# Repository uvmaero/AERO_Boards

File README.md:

# AERO_Boards
All the Boards We Make

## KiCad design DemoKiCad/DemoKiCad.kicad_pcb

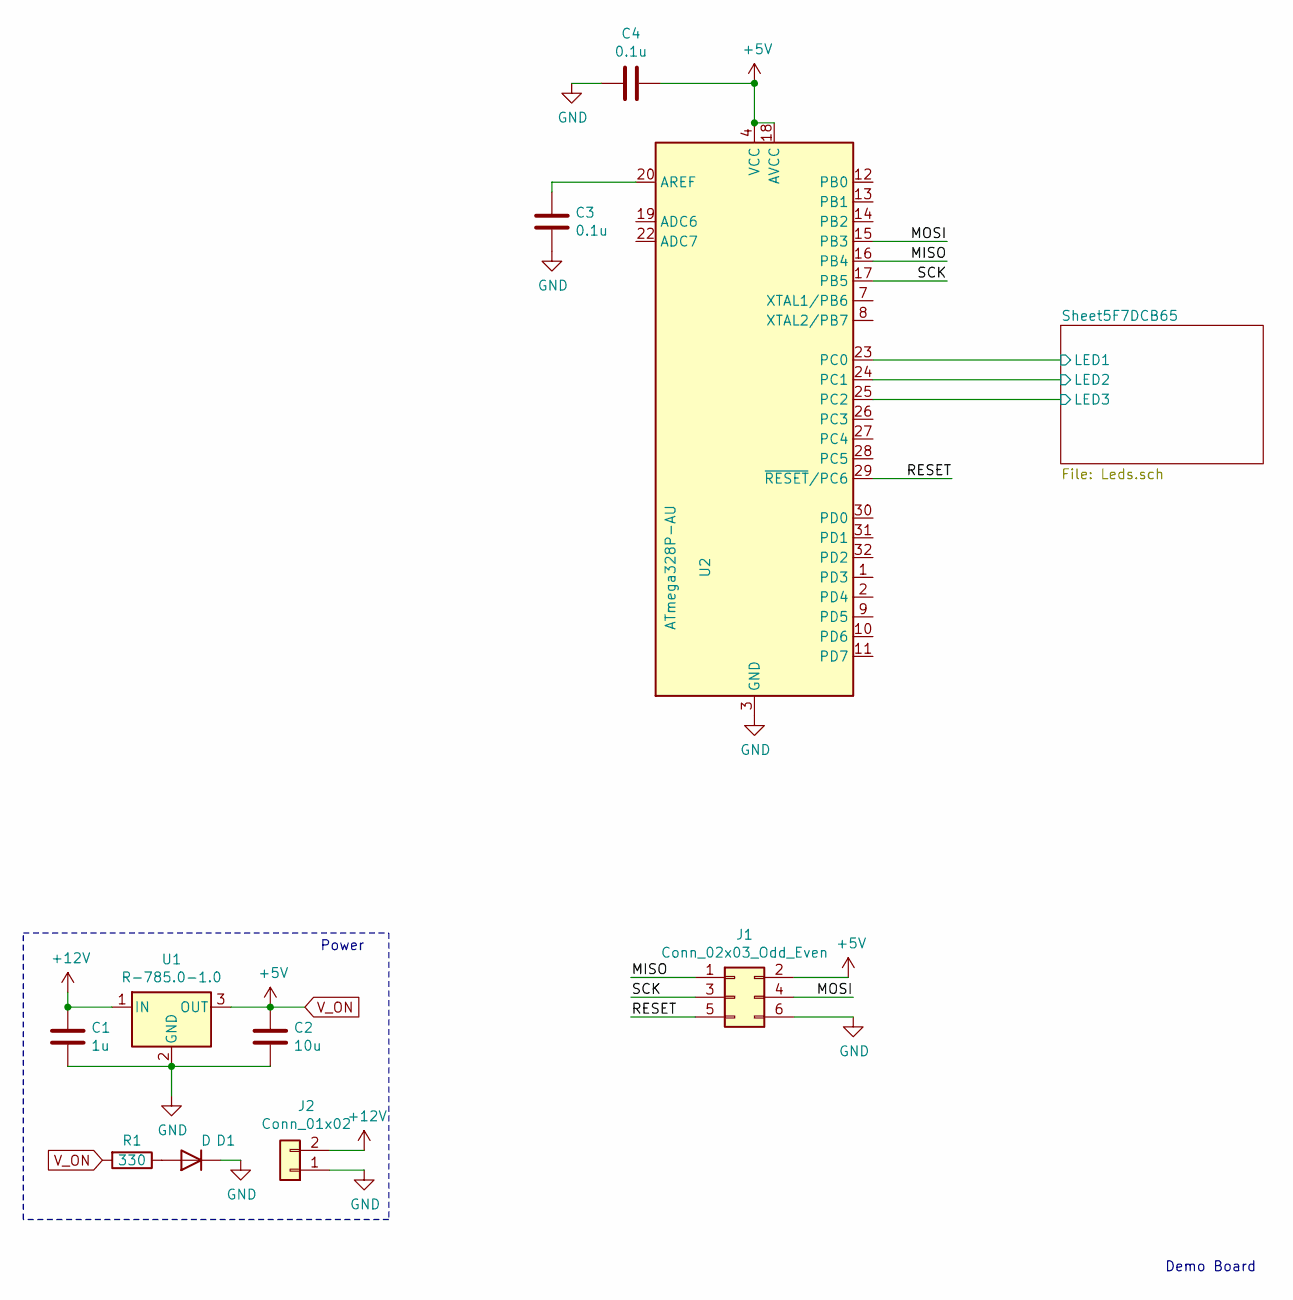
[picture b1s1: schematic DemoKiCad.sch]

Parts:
C1: 1u; C_0603_1608Metric_Pad1.05x0.95mm_HandSolder
C2: 10u; C_0603_1608Metric_Pad1.05x0.95mm_HandSolder
C3, C4: 0.1u; C_0603_1608Metric_Pad1.05x0.95mm_HandSolder
D1: D; D_0603_1608Metric_Pad1.05x0.95mm_HandSolder
J1: Conn_02x03_Odd_Even; PinHeader_2x03_P2.54mm_Vertical
J2: Conn_01x02; PinHeader_1x02_P2.54mm_Vertical
R1: 330; R_0603_1608Metric_Pad1.05x0.95mm_HandSolder
U1: R-785.0-1.0; Converter_DCDC_RECOM_R-78E-0.5_THT
U2: ATmega328P-AU; TQFP-32_7x7mm_P0.8mm

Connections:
+12V: C1.1, J2.2, U1.1 (IN)
/MISO: J1.1, U2.16 (PB4)
/MOSI: J1.4, U2.15 (PB3)
/RESET: J1.5, U2.29 (~RESET~/PC6)
/SCK: J1.3, U2.17 (PB5)
/Sheet5F7DCB65/LED1: U2.23 (PC0); also elsewhere on the board
/Sheet5F7DCB65/LED2: U2.24 (PC1); also elsewhere on the board
/Sheet5F7DCB65/LED3: U2.25 (PC2); also elsewhere on the board
GND: C1.2, C2.2, C3.2, C4.2, D1.1 (K), J1.6, J2.1, U1.2 (GND), U2.3 (GND), U2.5 (GND), U2.21 (GND); also elsewhere on the board
unnamed: C3.1, U2.20 (AREF)
unnamed: D1.2 (A), R1.1
V_ON: C2.1, C4.1, J1.2, R1.2, U1.3 (OUT), U2.4 (VCC), U2.6 (VCC), U2.18 (AVCC)

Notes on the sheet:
Demo Board
Power

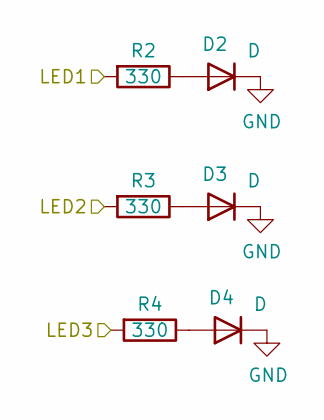
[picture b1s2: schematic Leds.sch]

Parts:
D2, D3, D4: D; D_0603_1608Metric_Pad1.05x0.95mm_HandSolder
R2, R3, R4: 330; R_0603_1608Metric_Pad1.05x0.95mm_HandSolder

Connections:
/Sheet5F7DCB65/LED1: R2.2; also elsewhere on the board
/Sheet5F7DCB65/LED2: R3.2; also elsewhere on the board
/Sheet5F7DCB65/LED3: R4.2; also elsewhere on the board
GND: D2.1 (K), D3.1 (K), D4.1 (K); also elsewhere on the board
unnamed: D2.2 (A), R2.1
unnamed: D3.2 (A), R3.1
unnamed: D4.2 (A), R4.1

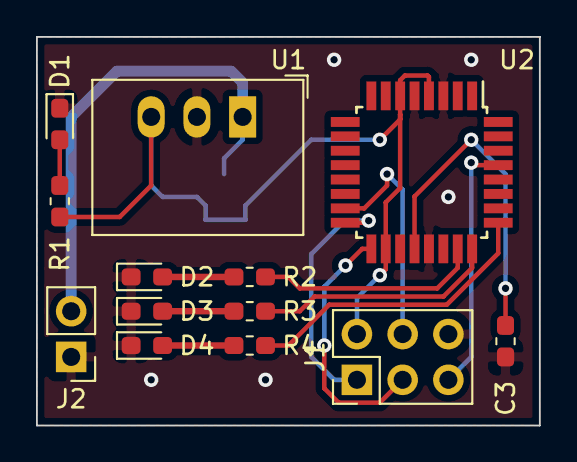
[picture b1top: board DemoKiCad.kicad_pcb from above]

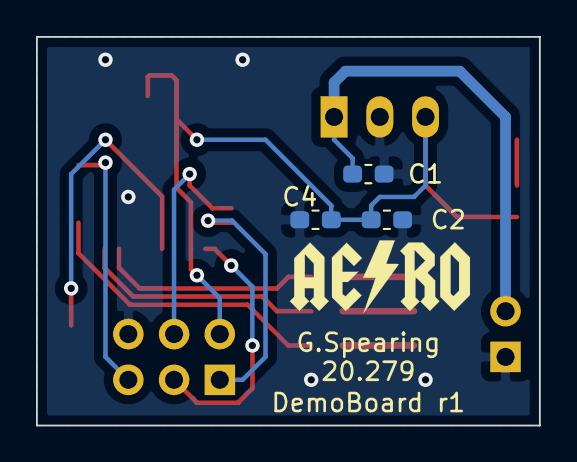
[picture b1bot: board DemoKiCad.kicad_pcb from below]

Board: 2 copper layers, 27.9 x 21.6 mm, 16 parts (3 on the bottom side), 15 nets.

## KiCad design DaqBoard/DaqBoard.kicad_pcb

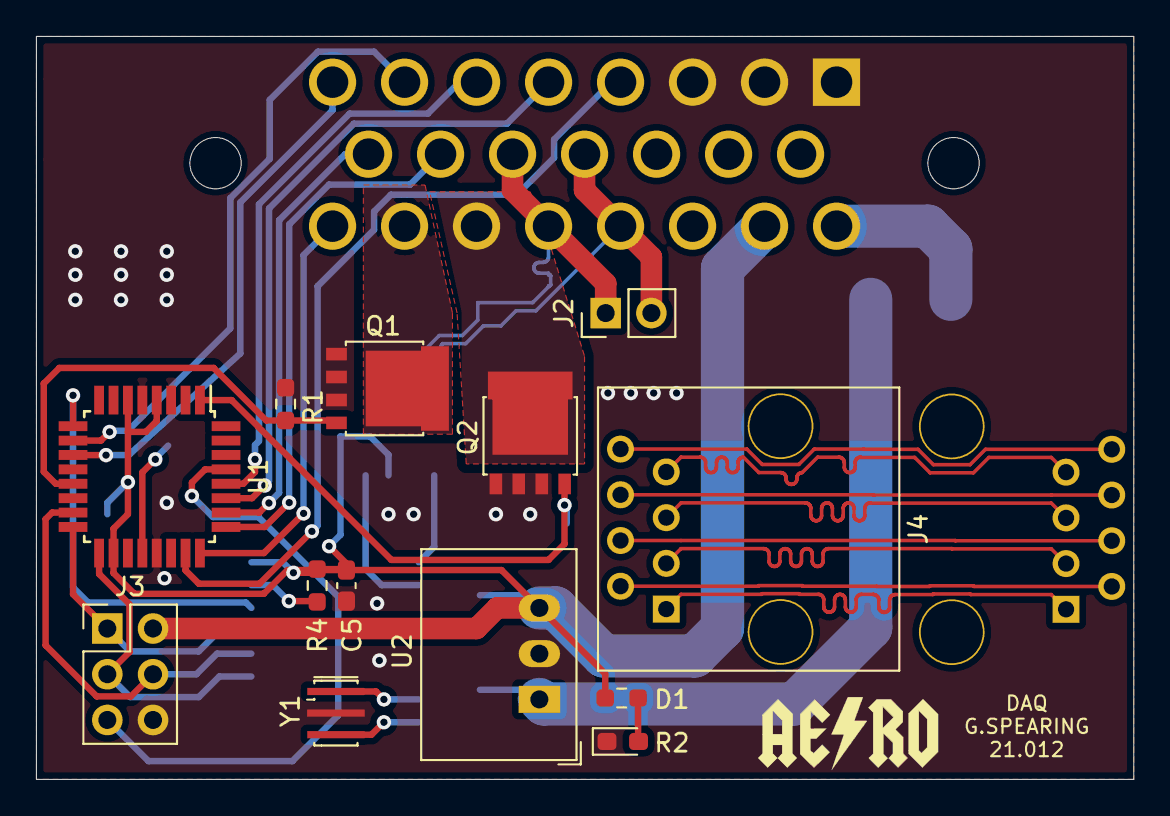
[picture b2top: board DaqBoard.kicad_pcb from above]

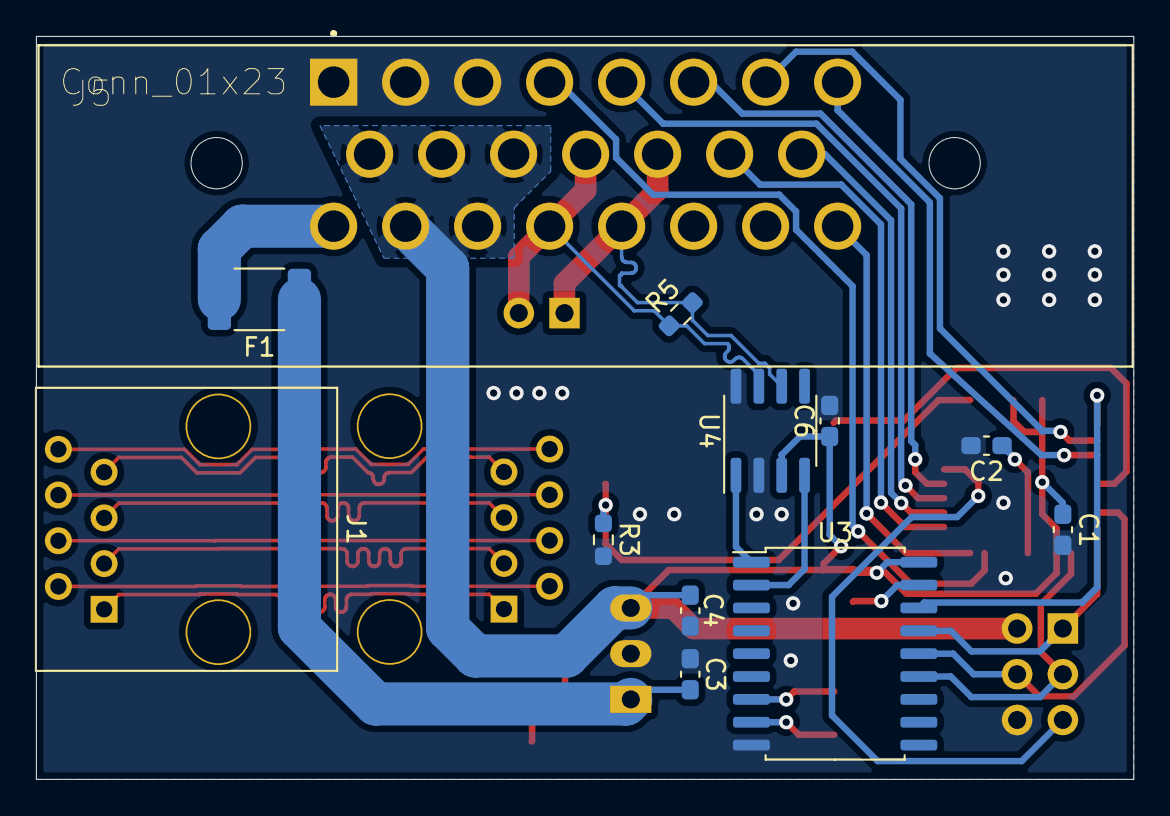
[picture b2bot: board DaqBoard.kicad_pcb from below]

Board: 2 copper layers, 61.0 x 41.3 mm, 25 parts (12 on the bottom side), 38 nets.

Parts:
C1, C2, C5, C6: 0.1u; C_0603_1608Metric_Pad1.08x0.95mm_HandSolder
C3: 1u; C_0603_1608Metric_Pad1.08x0.95mm_HandSolder
C4: 10u; C_0603_1608Metric_Pad1.08x0.95mm_HandSolder
D1: LED; LED_0603_1608Metric_Pad1.05x0.95mm_HandSolder
F1: MF-MSMF050; Fuse_1812_4532Metric_Pad1.30x3.40mm_HandSolder
J1, J4: RJ45; RJ45_TE_5569284-1-8P8CX_Vertical
J2: Conn_01x02; PinHeader_1x02_P2.54mm_Vertical
J3: Conn_02x03_Odd_Even; PinHeader_2x03_P2.54mm_Vertical
J5: Conn_01x23; TE_1-770669-1_23pin_Horizontal
Q1, Q2: PSMN5R2-60YL; LFPAK56
R1, R3, R4: 10K; R_0603_1608Metric_Pad0.98x0.95mm_HandSolder
R2: 330; R_0603_1608Metric_Pad0.98x0.95mm_HandSolder
R5: 120; R_0603_1608Metric_Pad0.98x0.95mm_HandSolder
U1: ATmega328P-AU; TQFP-32_7x7mm_P0.8mm
U2: R-785.0-1.0; Converter_DCDC_RECOM_R-78E-0.5_THT
U3: MCP2515-xSO; SOIC-18W_7.5x11.6mm_P1.27mm
U4: MCP2551-I-SN; SOIC-8_3.9x4.9mm_P1.27mm
Y1: 16MHz; Resonator_SMD_muRata_CSTxExxV-3Pin_3.0x1.1mm_HandSoldering

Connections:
+5V: C1.1, C4.1, C5.1, C6.1, J3.2, J5.9, J5.10, J5.11, J5.17, J5.18, R2.2, R4.1, U1.4, U1.6, U1.18, U2.3, U3.18, U4.3
+12V: F1.2, J5.16
/BRAKE_OUT: J5.22, Q1.5
/BRAKE_SIG: Q1.4, R1.1, U1.13
/CAN+: J2.2, J5.12, J5.19, R5.1, U4.7
/CAN-: J2.1, J5.13, J5.20, R5.2, U4.6
/CAN_CS: U1.9, U3.16
/CAN_Interface/RXCAN: U3.2, U4.4
/CAN_Interface/TXCAN: U3.1, U4.1
/DAMPER_L: J5.14, U1.25
/DAMPER_R: J5.15, U1.26
/E1_N: J1.2, J4.2
/E1_P: J1.1, J4.1
/E2_N: J1.4, J4.4
/E2_P: J1.3, J4.3
/E3_N: J1.6, J4.6
/E3_P: J1.5, J4.5
/E4_N: J1.8, J4.8
/E4_P: J1.7, J4.7
/FAN_OUT: J5.21, Q2.5
/FAN_SIG: Q2.4, R3.1, U1.1
/MISO: J3.1, U1.16, U3.15
/MOSI: J3.4, U1.15, U3.14
/RESET: J3.5, U1.29
/SCK: J3.3, U1.17, U3.13
/SENSOR_1: J5.7, U1.10
/SENSOR_2: J5.8, U1.11
/SENSOR_5: J5.5, U1.27
/SENSOR_6: J5.6, U1.28
/WHEEL_L: J5.4, U1.23
/WHEEL_R: J5.23, U1.24
GND: C1.2, C2.2, C3.2, C4.2, C5.2, C6.2, D1.1, J3.6, J5.1, J5.2, J5.3, Q1.1, Q1.2, Q1.3, Q2.1, Q2.2, Q2.3, R1.2, R3.2, U1.3, U1.5, U1.21, U2.2, U3.9, U4.2, U4.8, Y1.2
unnamed: C2.1, U1.20
unnamed: C3.1, F1.1, U2.1
unnamed: D1.2, R2.1
unnamed: R4.2, U3.17
unnamed: U3.7, Y1.1
unnamed: U3.8, Y1.3

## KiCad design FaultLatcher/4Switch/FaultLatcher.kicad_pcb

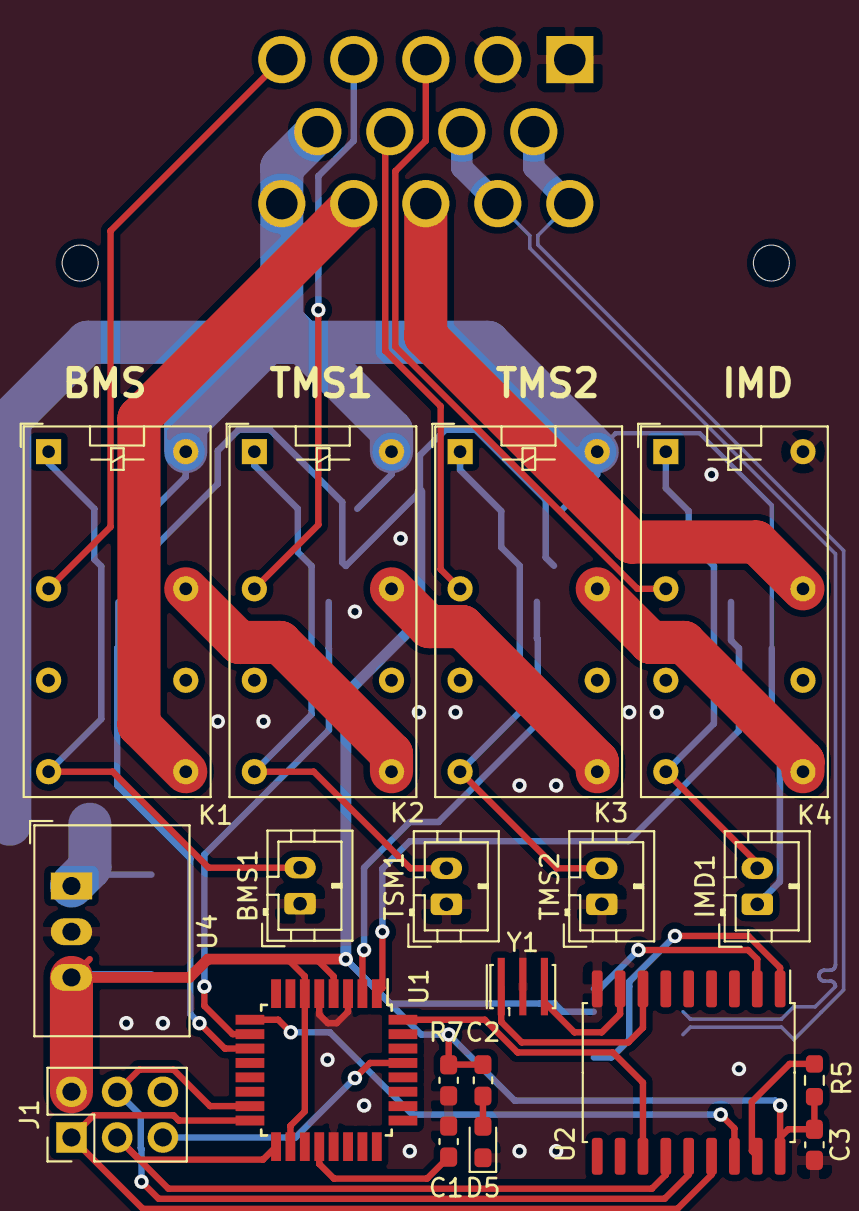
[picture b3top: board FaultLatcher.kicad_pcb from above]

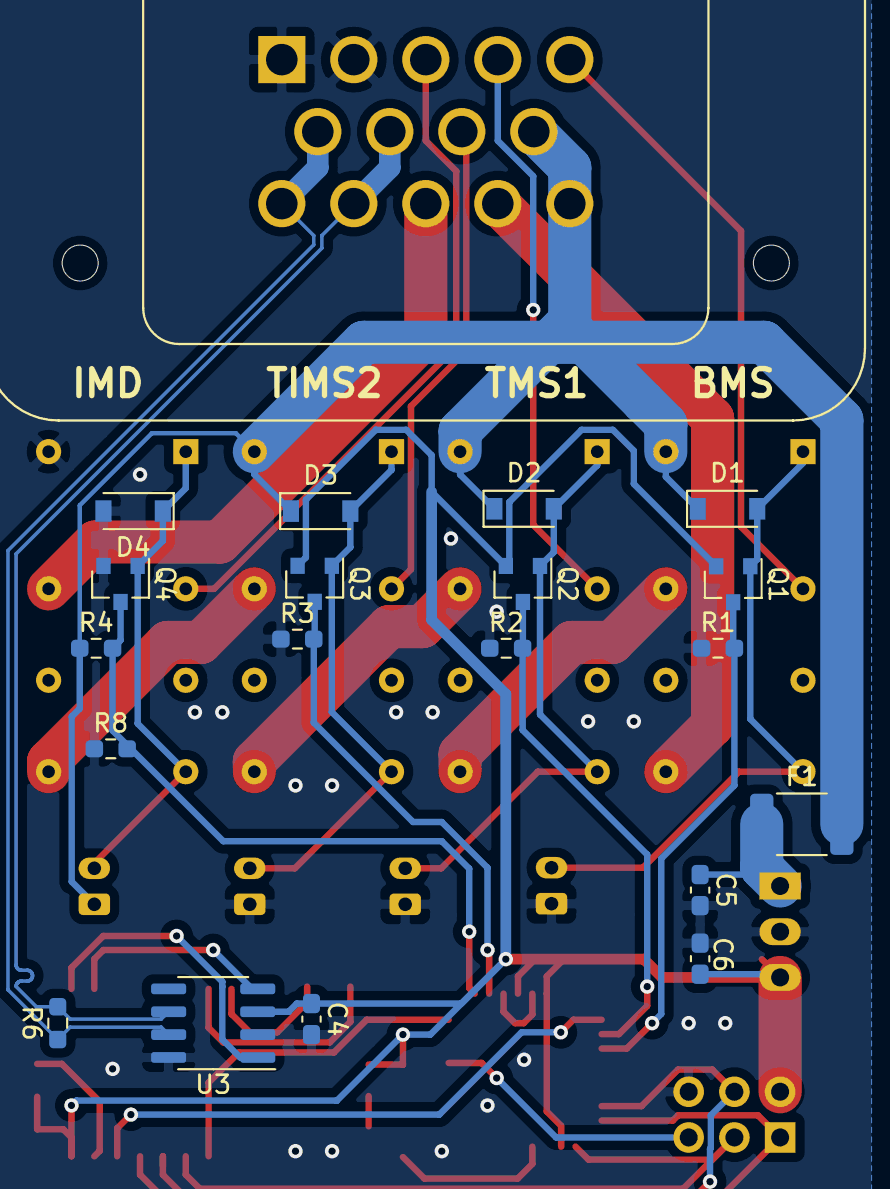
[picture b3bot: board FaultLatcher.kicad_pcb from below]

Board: 2 copper layers, 39 parts (20 on the bottom side), 36 nets.

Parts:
BMS1: SW_Push; JST_PH_B2B-PH-K_1x02_P2.00mm_Vertical
C1, C2: 0.1U; C_0603_1608Metric_Pad1.08x0.95mm_HandSolder
C3, C4: 0.1u; C_0603_1608Metric_Pad1.08x0.95mm_HandSolder
C5: 1u; C_0603_1608Metric_Pad1.08x0.95mm_HandSolder
C6: 10u; C_0603_1608Metric_Pad1.08x0.95mm_HandSolder
D1, D2, D3, D4: 1N4148; D_SOD-123
D5: LED; LED_0603_1608Metric_Pad1.05x0.95mm_HandSolder
F1: Polyfuse; Fuse_1812_4532Metric_Pad1.30x3.40mm_HandSolder
IMD1: SW_Push; JST_PH_B2B-PH-K_1x02_P2.00mm_Vertical
J1: Conn_02x03_Odd_Even; PinHeader_2x03_P2.54mm_Vertical
J2: Conn_01x14; TE_1-776262-1_14pin_Vertical
K1, K2, K3, K4: G5V-2; Relay_DPDT_Omron_G5V-2
Q1, Q2, Q3: BSS84; SOT-23
Q4: 2N7002; SOT-23
R1, R2, R3, R4: 10k; R_0603_1608Metric_Pad0.98x0.95mm_HandSolder
R5: 10K; R_0603_1608Metric_Pad0.98x0.95mm_HandSolder
R6: 120; R_0603_1608Metric_Pad0.98x0.95mm_HandSolder
R7: 330; Fuse_0603_1608Metric_Pad1.05x0.95mm_HandSolder
R8: 4.7k; R_0603_1608Metric_Pad0.98x0.95mm_HandSolder
TMS2: SW_Push; JST_PH_B2B-PH-K_1x02_P2.00mm_Vertical
TSM1: SW_Push; JST_PH_B2B-PH-K_1x02_P2.00mm_Vertical
U1: ATmega328P-AU; TQFP-32_7x7mm_P0.8mm
U2: MCP2515-xSO; SOIC-18W_7.5x11.6mm_P1.27mm
U3: MCP2551-I-SN; SOIC-8_3.9x4.9mm_P1.27mm
U4: R-785.0-1.0; Converter_DCDC_RECOM_R-78E-0.5_THT
Y1: 16MHz; Resonator_SMD_muRata_CSTxExxV-3Pin_3.0x1.1mm_HandSoldering

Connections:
+5V: C2.1, C3.1, C4.1, C6.1, J1.2, Q1.2, Q2.2, Q3.2, R5.1, R7.2, U1.4, U1.6, U1.18, U2.18, U3.3, U4.3
+12V: D1.1, D2.1, D3.1, F1.2, IMD1.1, J2.9, J2.14, K1.16, K2.16, K3.16, R4.1
/BMS_FAULT: J2.5, K1.4
/BMS_IND: Q1.3, R1.2, U1.11
/CAN+: J2.6, J2.10, R6.1, U3.7
/CAN-: J2.7, J2.11, R6.2, U3.6
/CAN_CS: U1.9, U2.16
/CAN_INT: U1.32, U2.12
/IMD_FAULT: J2.3, K4.4
/IMD_IND: Q4.3, R4.2, R8.2, U1.1
/LOOP_IN: J2.13, K1.9
/LOOP_OUT: J2.12, K4.13
/MISO: J1.1, U1.16, U2.15
/MOSI: J1.4, U1.15, U2.14
/RESET: J1.5, U1.29
/RXCAN: U2.2, U3.4
/SCK: J1.3, U1.17, U2.13
/TMS1_FAULT: J2.4, K2.4
/TMS1_IND: Q2.3, R2.2, U1.10
/TMS2_FAULT: J2.8, K3.4
/TMS2_IND: Q3.3, R3.2, U1.2
/TXCAN: U2.1, U3.1
GND: BMS1.1, C1.2, C2.2, C3.2, C4.2, C5.2, C6.2, D4.2, D5.1, J1.6, J2.1, J2.2, K4.16, Q4.2, R1.1, R2.1, R3.1, R8.1, TMS2.1, TSM1.1, U1.3, U1.5, U1.21, U2.9, U3.2, U3.8, U4.2, Y1.2
unnamed: BMS1.2, D1.2, K1.1, K1.8, Q1.1
unnamed: C1.1, U1.20
unnamed: C5.1, F1.1, U4.1
unnamed: D2.2, K2.1, K2.8, Q2.1, TSM1.2
unnamed: D3.2, K3.1, K3.8, Q3.1, TMS2.2
unnamed: D4.1, IMD1.2, K4.1, K4.8, Q4.1
unnamed: D5.2, R7.1
unnamed: K1.13, K2.9
unnamed: K2.13, K3.9
unnamed: K3.13, K4.9
unnamed: R5.2, U2.17
unnamed: U2.7, Y1.1
unnamed: U2.8, Y1.3

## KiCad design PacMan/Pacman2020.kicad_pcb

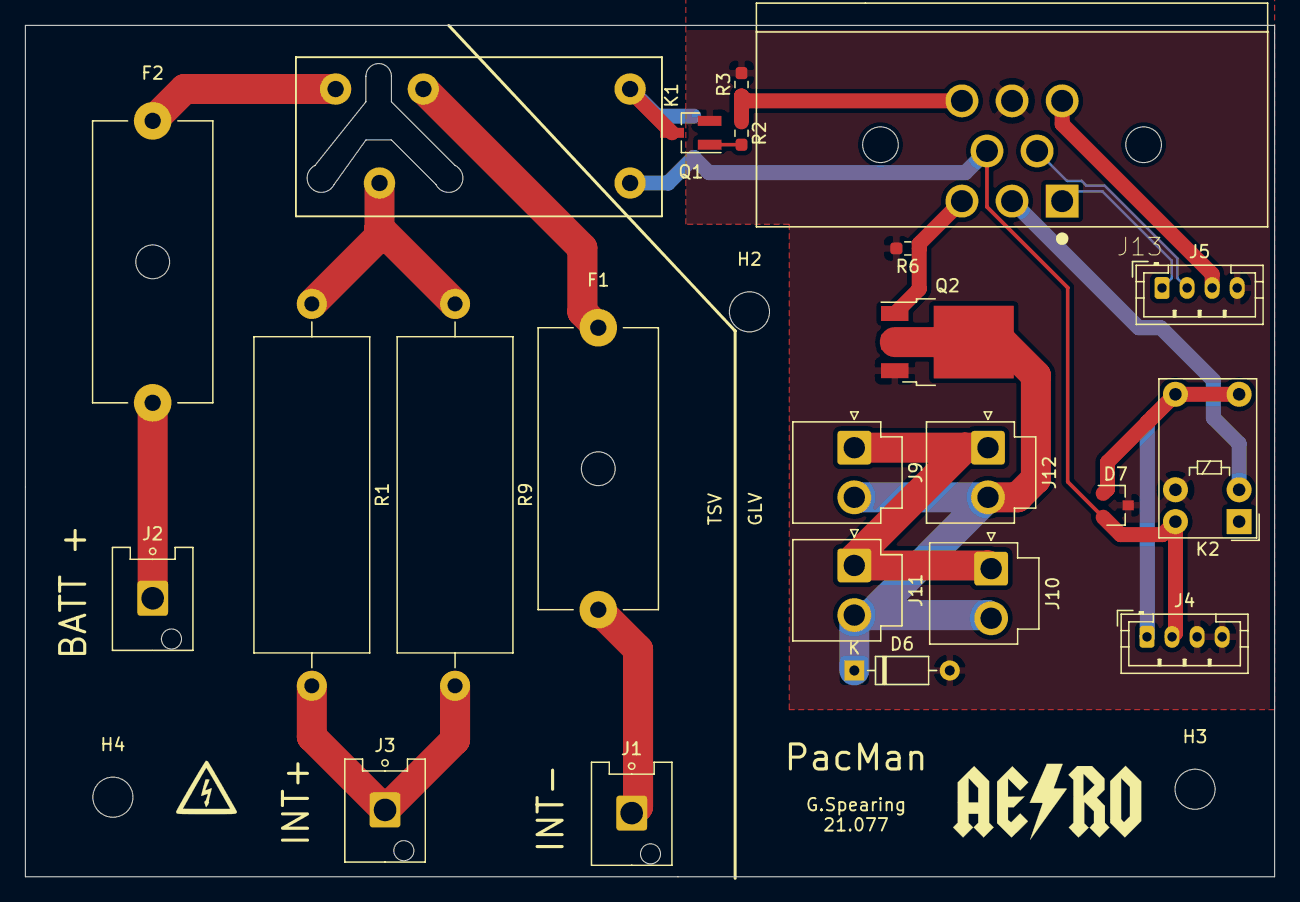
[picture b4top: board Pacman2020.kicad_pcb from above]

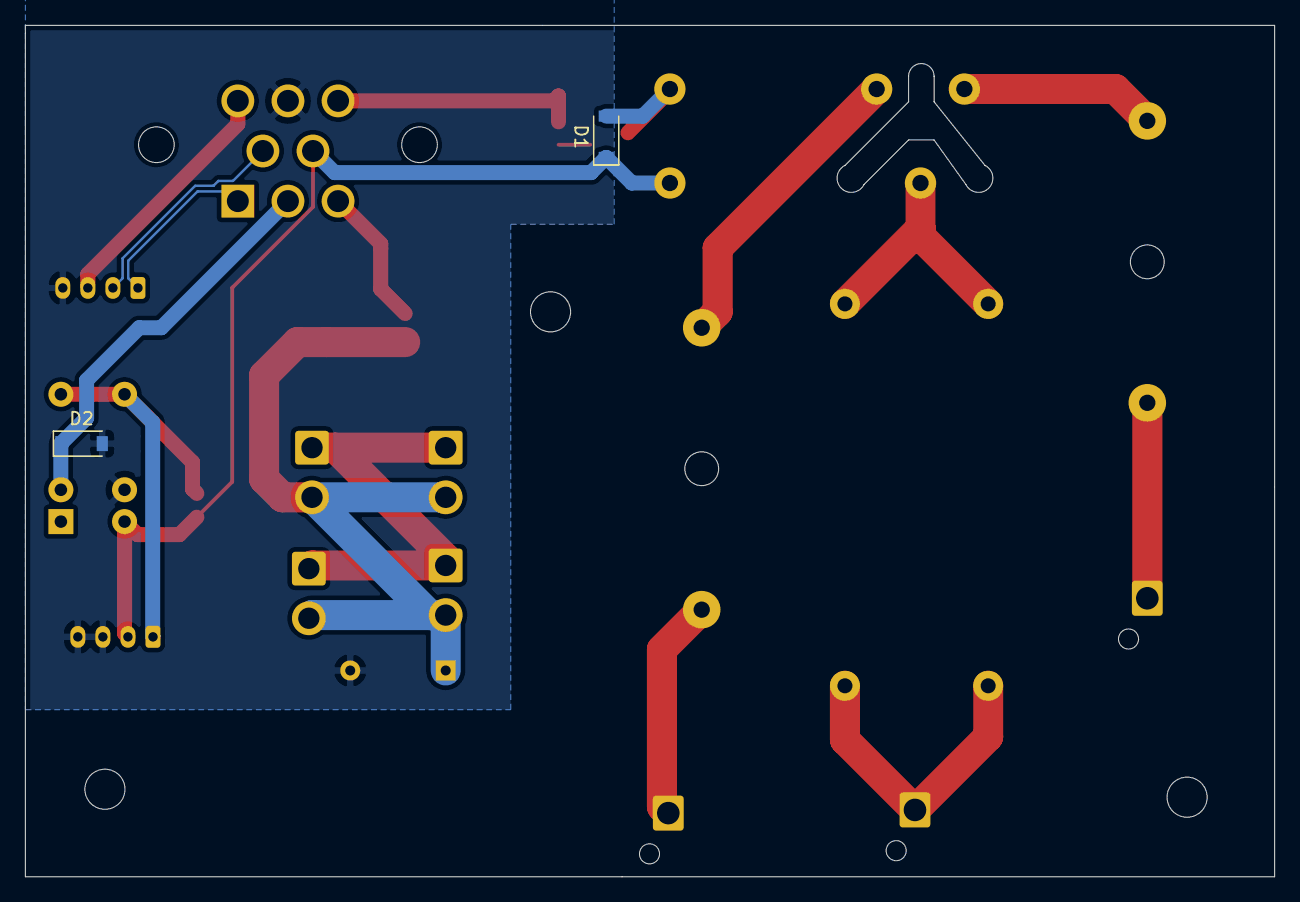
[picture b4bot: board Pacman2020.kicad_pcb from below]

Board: 2 copper layers, 99.7 x 67.9 mm, 29 parts (2 on the bottom side), 19 nets.

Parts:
D1, D2: D; D_SOD-123
D6: 1N4148; D_DO-35_SOD27_P7.62mm_Horizontal
D7: MMBZxx; SOT-23
F1, F2: 1A 300VDC; Fuseholder_Cylinder-5x20mm_Schurter_0031_8201_Horizontal_Op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
H2, H3, H4: MountingHole; MountingHole_3.2mm_M3
J1, J2, J3: DF22-1P-7.92DSA(05); Hirose_DF63R-1P-3.96DSA_1x01_P3.96mm_Vertical
J4: JST PH; JST_PH_B4B-PH-K_1x04_P2.00mm_Vertical
J5: Conn_01x04; JST_PH_B4B-PH-K_1x04_P2.00mm_Vertical
J9, J10, J11, J12: Conn_01x02; JST_VH_B2P-VH-B_1x02_P3.96mm_Vertical
J13: Conn_01x08; TE_1-776280-1_8pin_Horizontal
K1: G2RL
K2: G5V-1; Relay_SPDT_Omron_G5V-1
Q1: MMBT2222A; SOT-23_Handsoldering
Q2: Q_NMOS_GDS; TO-252-3_TabPin2
R1, R9: R; R_Axial_Power_L25.0mm_W9.0mm_P30.48mm
R2, R3: R; R_0603_1608Metric_Pad0.98x0.95mm_HandSolder
R6: 10k; R_0603_1608Metric_Pad0.98x0.95mm_HandSolder
Ref**: Val**; hv_small

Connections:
+12V: J5.3, J13.6
/12_IN: J9.1, J10.1, J11.1, J12.1
/CAN+: J5.1, J13.1
/CAN-: J5.2, J13.4
/CONTACTOR: D2.1, J13.2, K2.2
/FAN_CTRL: J13.3, Q2.1, R6.1
/FAN_OUT: D6.1, J9.2, J10.2, J11.2, J12.2, Q2.2
/PRECHARGE: J13.8, R2.1, R3.1
/SHUTDOWN_IN: D1.1, D7.2, J4.2, J13.5, K1.2, K2.10
/pre/discharge/AIR_B+: D7.1, J4.1, K2.5, K2.6
/pre/discharge/BATT+: F2.2, J2.1
/pre/discharge/INT+: J3.1, R1.2, R9.2
/pre/discharge/INT-: F1.2, J1.1
GND: D2.2, D6.2, D7.3, J4.3, J4.4, J5.4, J13.7, K2.9, Q1.2, Q2.3, R3.2, R6.2
unnamed: D1.2, K1.9, Q1.3
unnamed: F1.1, K1.1
unnamed: F2.1, K1.10
unnamed: K1.5, R1.1, R9.1
unnamed: Q1.1, R2.2

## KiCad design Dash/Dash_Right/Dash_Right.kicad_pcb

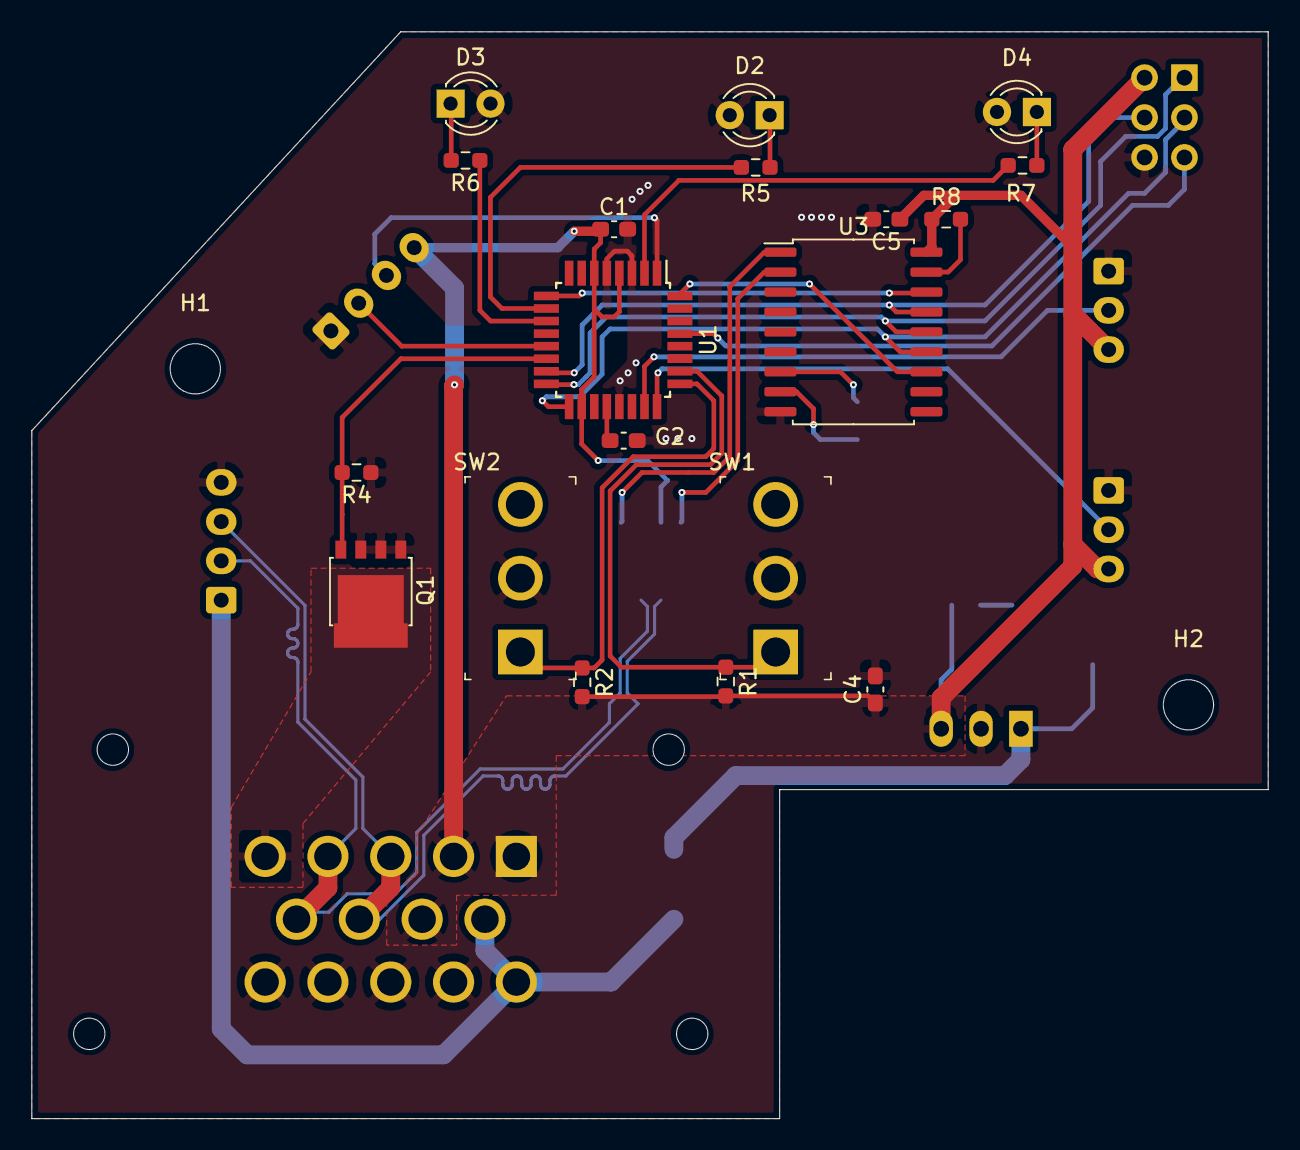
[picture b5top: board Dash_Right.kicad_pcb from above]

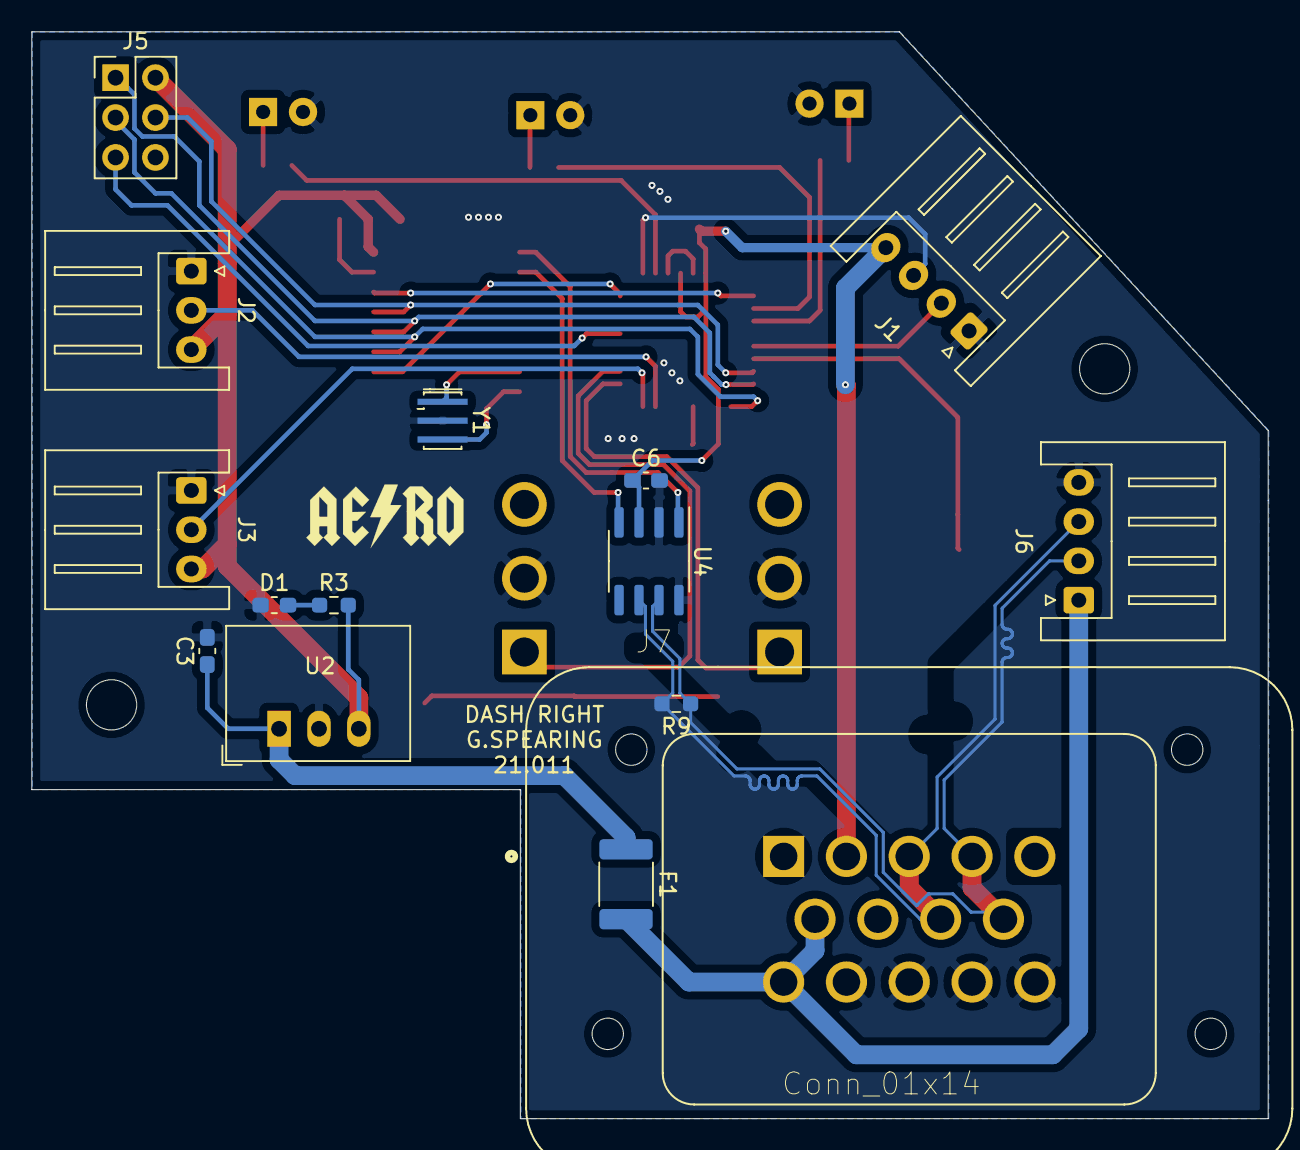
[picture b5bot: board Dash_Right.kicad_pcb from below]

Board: 2 copper layers, 78.7 x 69.2 mm, 36 parts (15 on the bottom side), 33 nets.

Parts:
C1, C2, C5, C6: 0.1u; C_0603_1608Metric_Pad1.08x0.95mm_HandSolder
C3: 1u; C_0603_1608Metric_Pad1.08x0.95mm_HandSolder
C4: 10u; C_0603_1608Metric_Pad1.08x0.95mm_HandSolder
D1: LED; Fuse_0603_1608Metric_Pad1.05x0.95mm_HandSolder
D2, D3, D4: LED; LED_D3.0mm
F1: MF-MSMF050; Fuse_1812_4532Metric_Pad1.30x3.40mm_HandSolder
H1, H2: MountingHole; MountingHole_3.2mm_M3
J1, J6: Conn_01x04; JST_XH_S4B-XH-A_1x04_P2.50mm_Horizontal
J2, J3: Conn_01x03; JST_XH_S3B-XH-A_1x03_P2.50mm_Horizontal
J5: Conn_02x03_Odd_Even; PinHeader_2x03_P2.54mm_Vertical
J7: Conn_01x14; TE_1-776262-1_14pin_Vertical
Q1: PSMN5R2-60YL; LFPAK56
R1, R2, R4, R8: 10K; R_0603_1608Metric_Pad0.98x0.95mm_HandSolder
R3, R5, R6, R7: 330; R_0603_1608Metric_Pad0.98x0.95mm_HandSolder
R9: 120; R_0603_1608Metric_Pad0.98x0.95mm_HandSolder
SW1, SW2: SW_SPDT; Toggle_Switch_100SP1T1B4M2QE
U1: ATmega328P-AU; TQFP-32_7x7mm_P0.8mm
U2: R-785.0-1.0; Converter_DCDC_RECOM_R-78E-0.5_THT
U3: MCP2515-xSO; SOIC-18W_7.5x11.6mm_P1.27mm
U4: MCP2551-I-SN; SOIC-8_3.9x4.9mm_P1.27mm
Y1: 16MHz; Resonator_SMD_muRata_CSTxExxV-3Pin_3.0x1.1mm_HandSoldering

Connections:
+5V: C1.1, C4.1, C5.1, C6.1, J1.4, J2.3, J3.3, J5.2, J7.1, J7.2, J7.7, R1.2, R2.2, R3.2, R8.1, U1.4, U1.6, U1.18, U2.3, U3.18, U4.3
+12V: F1.2, J6.1, J7.6, J7.10
/BMS_LED: R7.1, U1.2
/CAN+: J6.2, J7.4, J7.9, R9.1, U4.7
/CAN-: J6.3, J7.3, J7.8, R9.2, U4.6
/CAN_CS: U1.9, U3.16
/CAN_INT: U1.32, U3.12
/CAN_Interface/RXCAN: U3.2, U4.4
/CAN_Interface/TXCAN: U3.1, U4.1
/COAST: J2.2, U1.23
/COOLING: R1.1, SW1.1, U1.26
/DIRECTION: R2.1, SW2.1, U1.25
/IMD_LED: R5.1, U1.10
/MISO: J5.1, U1.16, U3.14
/MOSI: J5.4, U1.15, U3.15
/REGEN: J3.2, U1.24
/RESET: J5.5, U1.29
/RTD_BTN: J1.3, U1.1
/RTD_IND: Q1.4, R4.2, U1.14
/RTD_IND_OUT: J7.5, Q1.5
/RTD_LED: J1.2, U1.13
/SCK: J5.3, U1.17, U3.13
/TMS_LED: R6.1, U1.11
GND: C1.2, C2.2, C3.2, C4.2, C5.2, C6.2, D1.1, D2.2, D3.2, D4.2, J1.1, J2.1, J3.1, J5.6, J6.4, J7.11, J7.12, J7.13, J7.14, Q1.1, Q1.2, Q1.3, R4.1, SW1.2, SW2.2, U1.3, U1.5, U1.21, U2.2, U3.9, U4.2, U4.8, Y1.2
unnamed: C2.1, U1.20
unnamed: C3.1, F1.1, U2.1
unnamed: D1.2, R3.1
unnamed: D2.1, R5.2
unnamed: D3.1, R6.2
unnamed: D4.1, R7.2
unnamed: R8.2, U3.17
unnamed: U3.7, Y1.1
unnamed: U3.8, Y1.3

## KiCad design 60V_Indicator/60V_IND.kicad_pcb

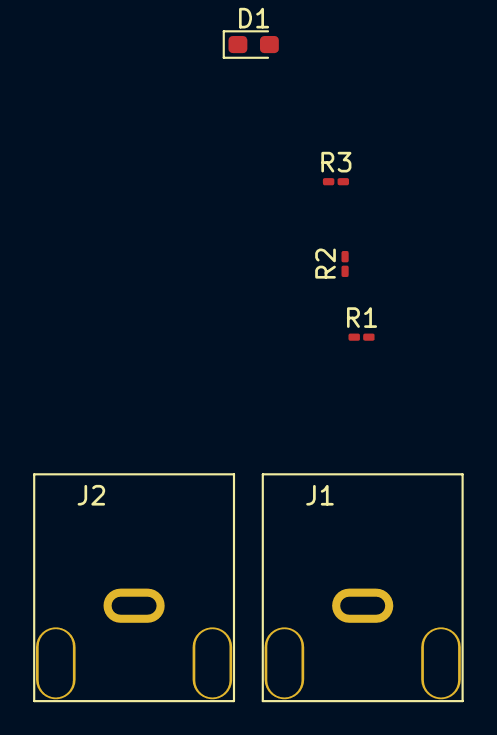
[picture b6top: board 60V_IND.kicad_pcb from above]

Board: 2 copper layers, 6 parts (0 on the bottom side), 5 nets, no tracks yet.

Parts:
D1: LED; LED_0603_1608Metric_Pad1.05x0.95mm_HandSolder
J1, J2: Conn_01x01; DF22-1P
R1, R2, R3: R; R_0201_0603Metric_Pad0.64x0.40mm_HandSolder

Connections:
unnamed: D1.1, J2.1
unnamed: D1.2, R3.2
unnamed: J1.1, R1.1
unnamed: R1.2, R2.1
unnamed: R2.2, R3.1

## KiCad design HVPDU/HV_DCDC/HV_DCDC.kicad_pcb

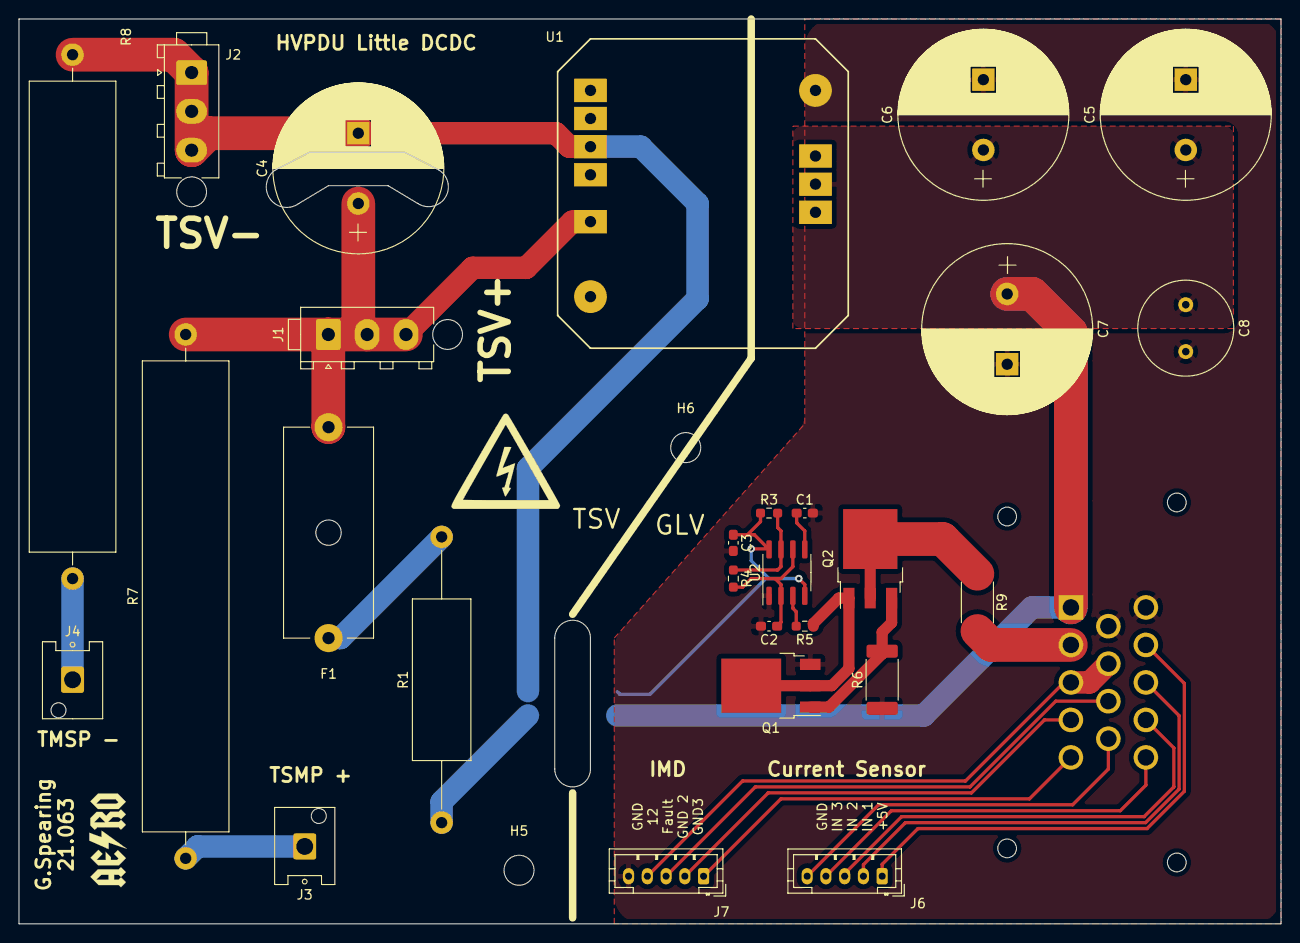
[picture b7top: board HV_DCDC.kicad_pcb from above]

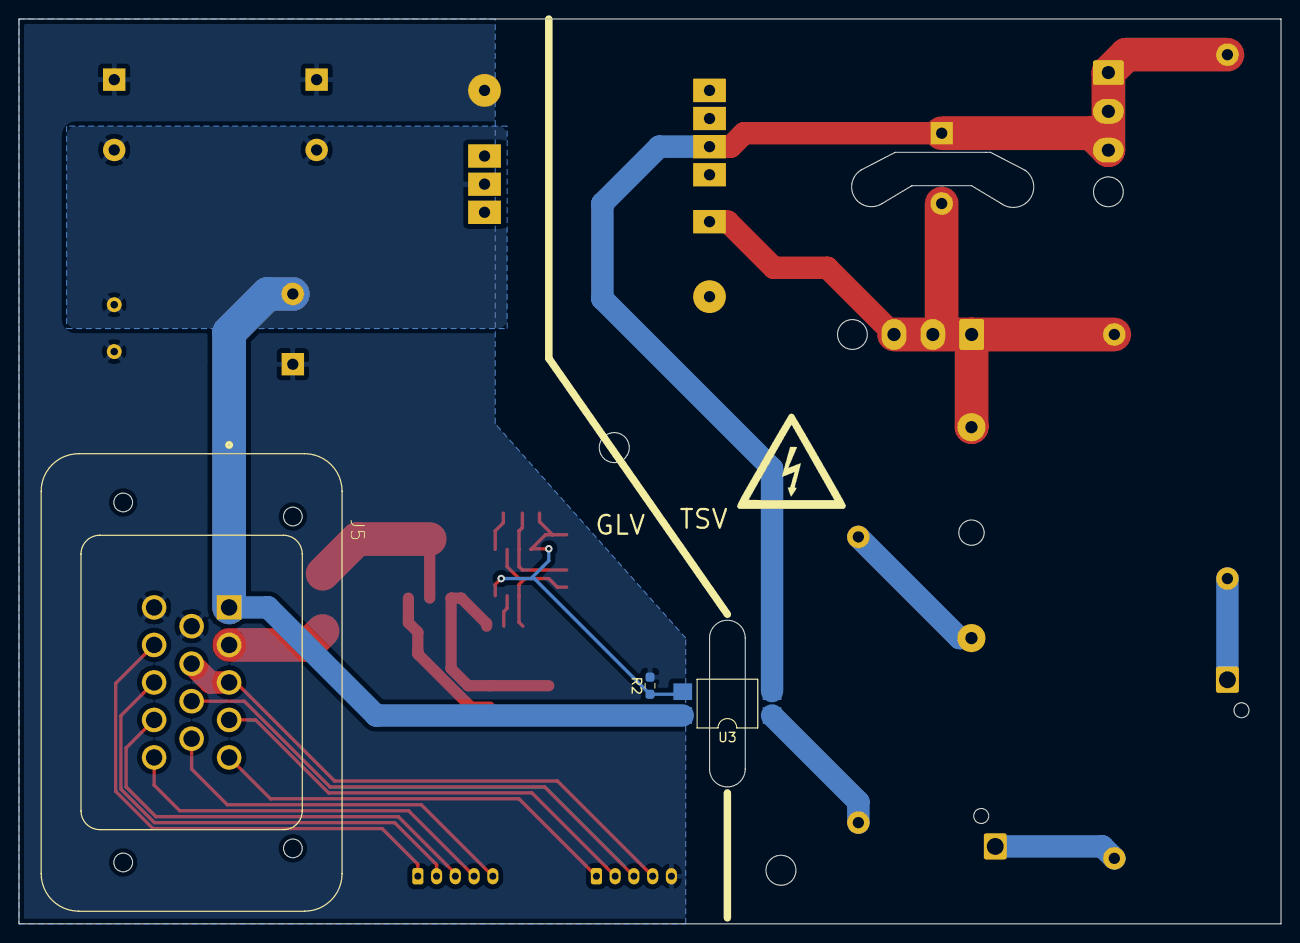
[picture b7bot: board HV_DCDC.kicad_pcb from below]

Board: 2 copper layers, 134.6 x 96.5 mm, 34 parts (4 on the bottom side), 26 nets.

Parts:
C1, C3: 0.1u; C_0603_1608Metric_Pad1.08x0.95mm_HandSolder
C2: 1u; C_0603_1608Metric_Pad1.08x0.95mm_HandSolder
C4: 33uF 450V; CAP_18x25_NICH
C5, C6: 330uF 25V; CAP_18x25_NICH
C7: 47uF 25V; CAP_18x25_NICH
C8: 0.1uF 50V; C_Radial_D10.0mm_H12.5mm_P5.00mm
F1: 0ADK-2.5A; Fuseholder_Cylinder-5x20mm_Schurter_0031_8201_Horizontal_Op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
H5, H6: M3; MountingHole_3.2mm_M3
J1, J2: TE_Connector; TE_MATE-N-LOK_1-770870-x_1x03_P4.14mm_Vertical
J3, J4: DF22; Hirose_DF63M-1P-3.96DSA_1x01_P3.96mm_Vertical
J5: Conn_01x14; TE_1-776262-1_14pin_Vertical
J6, J7: Conn_01x05; JST_PH_B5B-PH-K_1x05_P2.00mm_Vertical
Q1, Q2: 040N03LG; TO-252-3_TabPin2
R1: 39k; R_Axial_DIN0617_L17.0mm_D6.0mm_P30.48mm_Horizontal
R2, R5: 10k; R_0603_1608Metric_Pad0.98x0.95mm_HandSolder
R3: 100k; R_0603_1608Metric_Pad0.98x0.95mm_HandSolder
R4: 235k; R_0603_1608Metric_Pad0.98x0.95mm_HandSolder
R6: 0.75; R_2512_6332Metric_Pad1.40x3.35mm_HandSolder
R7, R8: 10k; R_Axial_Power_L50.0mm_W9.0mm_P55.88mm
R9: 1.0; R_2512_6332Metric_Pad1.40x3.35mm_HandSolder
Ref**: Val**; hv_big
Ref**#2: Val**; hv_big
U1: EPM1510SJ
U2: LM555; SOIC-8_3.9x4.9mm_P1.27mm
U3: LTV-817S; SMDIP-4_W9.53mm

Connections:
+5V: J5.11, J6.1
+12V: J5.3, J5.7, J7.4
/+DCDC_OUT: C5.1, C6.1, C7.1, C8.1, J5.1, U1.5, U3.4
/Fault_IND: J5.8, J7.3
/GND_Chassis: J5.4, J7.2
/GND_Electric: J5.5, J7.1
/INPUT1: J5.12, J6.2
/INPUT2: J5.13, J6.3
/INPUT3: J5.14, J6.4
/RED_ON_GND: J5.2, R9.2
/TSAL_TSV+: F1.1, R1.2
/TSAL_on_HVPDU/555_OUT: R5.2, U2.3
/TSAL_on_HVPDU/pass: C2.1, R4.2, U2.2, U2.6
/TSV+: C4.1, F1.2, J1.1, J1.2, J1.3, R7.2, U1.12
/TSV+_TSMP: J3.1, R7.1
/TSV-: C4.2, J2.1, J2.2, J2.3, R8.2, U1.10, U3.2
/TSV-_TSMP: J4.1, R8.1
GND: C1.2, C2.2, C3.2, C5.2, C6.2, C7.2, C8.2, J5.6, J5.10, J7.5, Q1.3, R2.2, R6.1, U1.7, U2.1
GNDREF: J5.9, J6.5
unnamed: C1.1, U2.5
unnamed: Q1.1, Q2.3, R6.2
unnamed: Q1.2, Q2.1, R5.1
unnamed: Q2.2, R9.1
unnamed: R1.1, U3.1
unnamed: R3.2, R4.1, U2.7
VCC: C3.1, R2.1, R3.1, U2.4, U2.8, U3.3
